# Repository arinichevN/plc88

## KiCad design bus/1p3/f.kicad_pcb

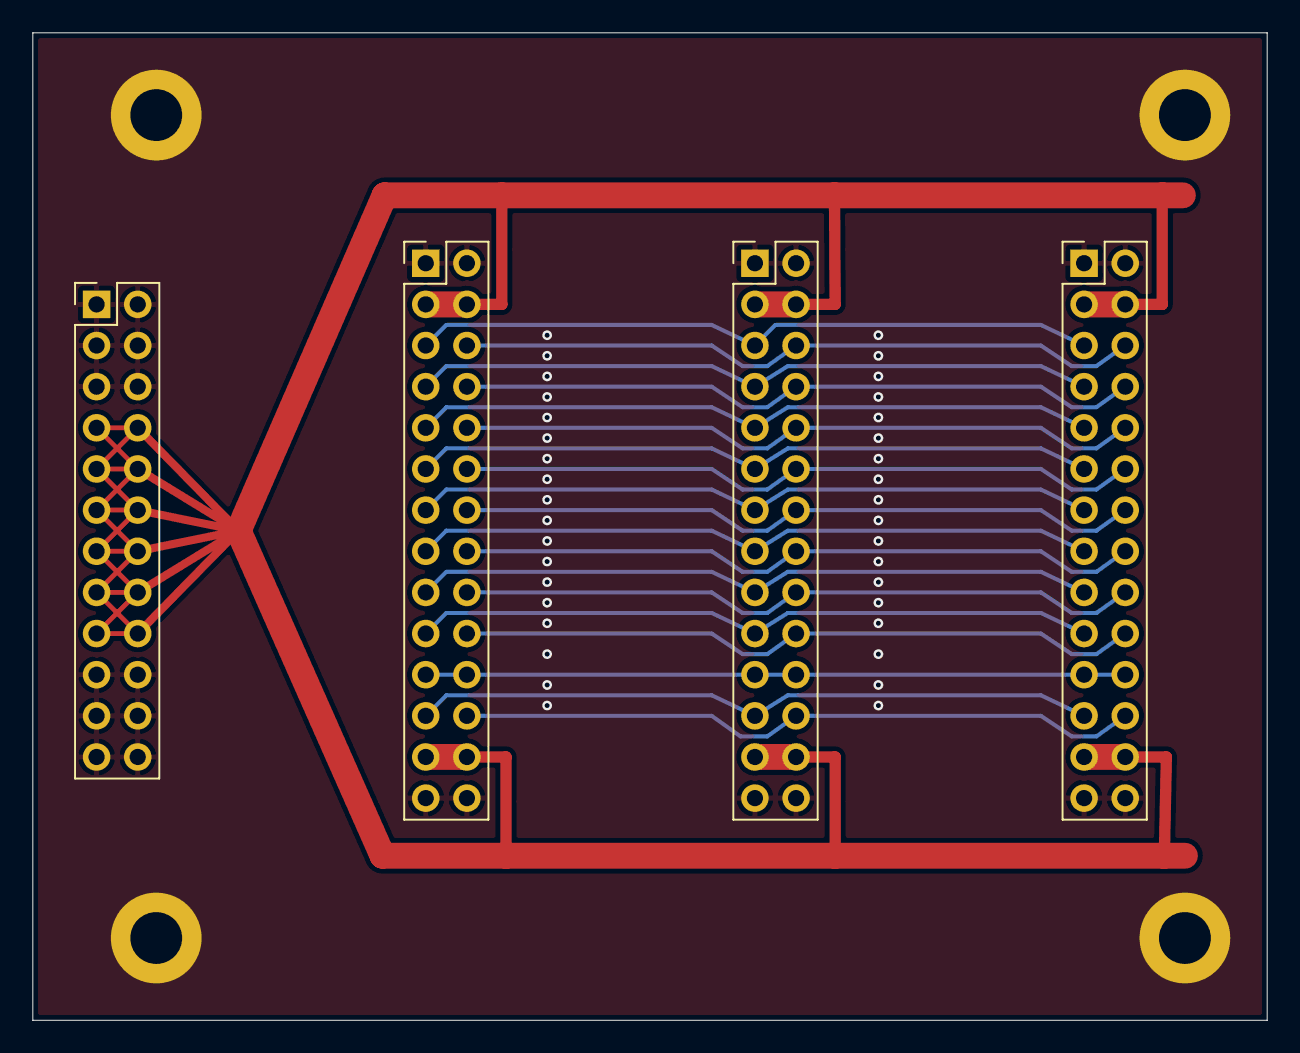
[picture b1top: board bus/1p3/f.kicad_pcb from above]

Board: 2 copper layers, 76.2 x 61.0 mm, 8 parts (0 on the bottom side), 21 nets.

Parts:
H1, H2, H3, H4: MountingHole_Pad; MountingHole_3.2mm_M3_DIN965_Pad
J1: bus_power_i; PinHeader_2x12_P2.54mm_Vertical
J2, J3, J4: bus_i; PinHeader_2x14_P2.54mm_Vertical

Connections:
A0: J2.5, J3.5, J4.5
A1: J2.7, J3.7, J4.7
A2: J2.9, J3.9, J4.9
A3: J2.11, J3.11, J4.11
A4: J2.13, J3.13, J4.13
A5: J2.15, J3.15, J4.15
A6: J2.17, J3.17, J4.17
A7: J2.19, J3.19, J4.19
CLK: J2.21, J2.22, J3.21, J3.22, J4.21, J4.22
D0: J2.6, J3.6, J4.6
D1: J2.8, J3.8, J4.8
D2: J2.10, J3.10, J4.10
D3: J2.12, J3.12, J4.12
D4: J2.14, J3.14, J4.14
D5: J2.16, J3.16, J4.16
D6: J2.18, J3.18, J4.18
D7: J2.20, J3.20, J4.20
GND: H1.1, H2.1, H3.1, H4.1, J1.1, J1.2, J1.3, J1.4, J1.5, J1.6, J1.19, J1.20, J1.21, J1.22, J1.23, J1.24, J2.1, J2.2, J2.27, J2.28, J3.1, J3.2, J3.27, J3.28, J4.1, J4.2, J4.27, J4.28
RD: J2.23, J3.23, J4.23
VP: J1.7, J1.8, J1.9, J1.10, J1.11, J1.12, J1.13, J1.14, J1.15, J1.16, J1.17, J1.18, J2.3, J2.4, J2.25, J2.26, J3.3, J3.4, J3.25, J3.26, J4.3, J4.4, J4.25, J4.26
WR: J2.24, J3.24, J4.24

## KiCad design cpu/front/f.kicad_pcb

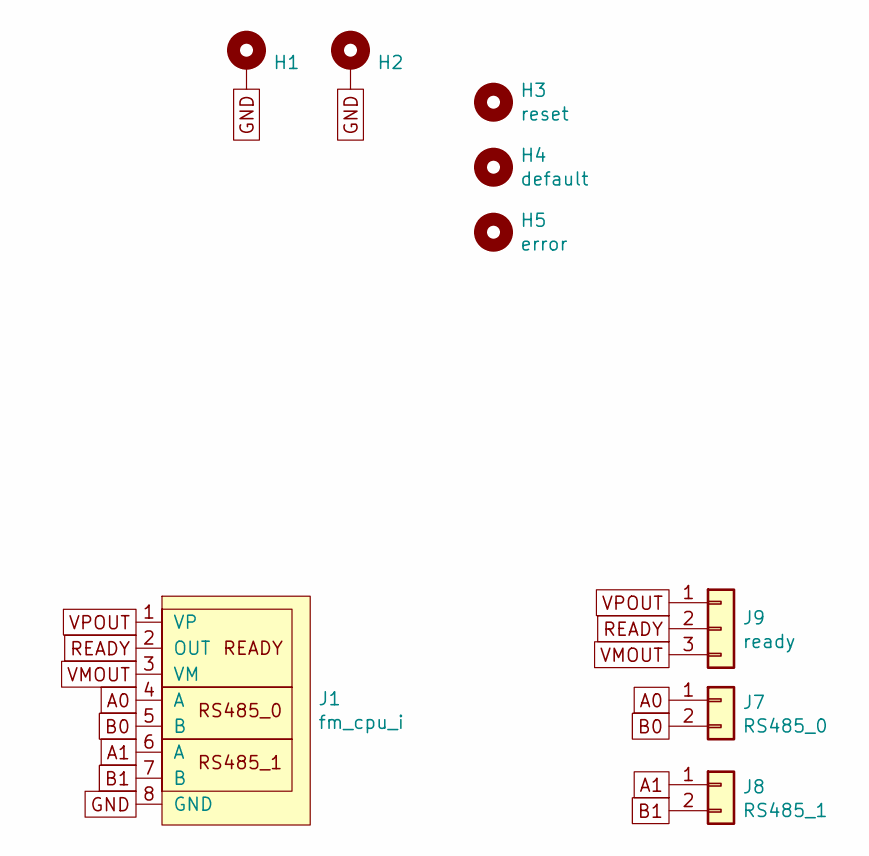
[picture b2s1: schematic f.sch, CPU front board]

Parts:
H1, H2: MountingHole_Pad; MountingHole_3.2mm_M3_Pad
H3: reset; MountingHole_3.5mm
H4: default; MountingHole_3.5mm
H5: error; MountingHole_2.1mm
J1: fm_cpu_i
J7: RS485_0; PhoenixContact_MCV_1,5_2-G-3.81_1x02_P3.81mm_Vertical
J8: RS485_1; PhoenixContact_MCV_1,5_2-G-3.81_1x02_P3.81mm_Vertical
J9: ready; PhoenixContact_MCV_1,5_3-G-3.81_1x03_P3.81mm_Vertical

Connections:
A0: J1.4 (A), J7.1
A1: J1.6 (A), J8.1
B0: J1.5 (B), J7.2
B1: J1.7 (B), J8.2
GND: H1.1, H2.1, J1.8 (GND)
READY: J1.2 (OUT), J9.2
VMOUT: J1.3 (VM), J9.3
VPOUT: J1.1 (VP), J9.1

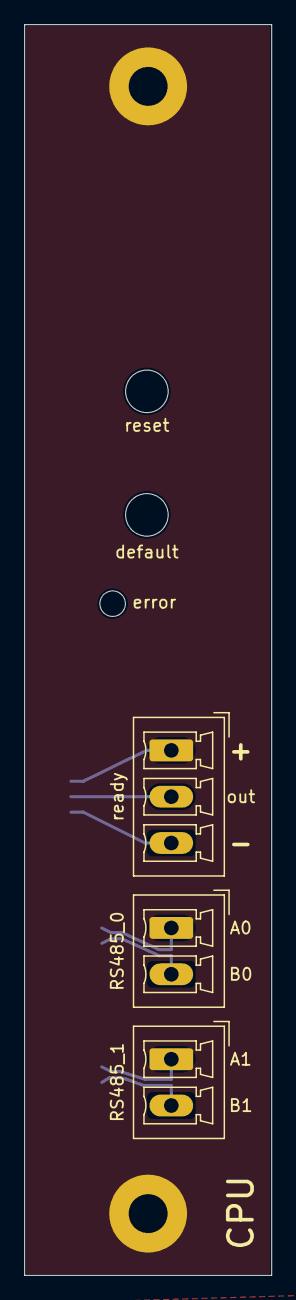
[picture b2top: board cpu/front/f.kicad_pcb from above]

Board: 2 copper layers, 20.3 x 102.9 mm, 9 parts (0 on the bottom side), 8 nets.

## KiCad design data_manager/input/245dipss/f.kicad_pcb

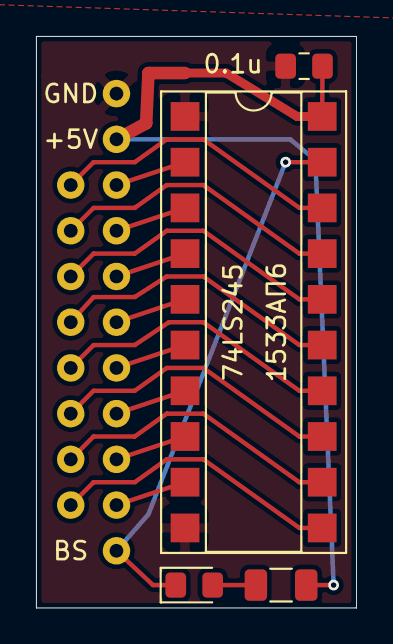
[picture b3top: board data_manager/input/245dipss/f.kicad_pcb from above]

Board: 2 copper layers, 17.8 x 31.8 mm, 5 parts (0 on the bottom side), 20 nets.

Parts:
C1: 0.1u; C_0805_2012Metric_Pad1.15x1.40mm_HandSolder
D3: LED; LED_0805_2012Metric_Pad1.15x1.40mm_HandSolder
J1: data_manager_i; data_manager_im
R5: 1k; R_1206_3216Metric
U1: 74LS245; DIP-20_W7.62mm_SMDSocket_SmallPads

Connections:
+5V: C1.2, J1.18, R5.2, U1.20
BD0: J1.1, U1.18
BD1: J1.3, U1.17
BD2: J1.5, U1.16
BD3: J1.7, U1.15
BD4: J1.9, U1.14
BD5: J1.11, U1.13
BD6: J1.13, U1.12
BD7: J1.15, U1.11
BS: D3.1, J1.19, U1.19
D0: J1.2, U1.2
D1: J1.4, U1.3
D2: J1.6, U1.4
D3: J1.8, U1.5
D4: J1.10, U1.6
D5: J1.12, U1.7
D6: J1.14, U1.8
D7: J1.16, U1.9
GND: C1.1, J1.17, U1.1, U1.10
unnamed: D3.2, R5.1
